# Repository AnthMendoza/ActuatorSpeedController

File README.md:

# FOC BLDC Servo Motor Controller

This board is a three phase field oriented control (FOC) motor controller for a brushless DC (BLDC) servo motor with an encoder. It combines a 32 bit microcontroller, a three-phase gate driver, six external power MOSFETs, phase current sensing, bus voltage sensing, motor temperature sensing, and encoder feedback.

## Functional overview

| Function | Main parts / nets | Purpose |
|---|---|---|
| MCU and control | STM32F405RGTx (U2) | Runs FOC, PWM generation, feedback processing, communications, and protection logic |
| Three-phase gate drive | DRV8323RSRGZT (U1) | Converts MCU PWM commands into high- and low-side MOSFET gate drive |
| Power stage | Q1-Q6, IQE022N06LM5CG | Six-switch inverter producing phase_A, phase_B, and phase_C |
| Current measurement | R8-R10, 1 mOhm | Low-side shunt current sensing for phases A, B, and C |
| Rotor position | AS5147U (shown on the drive sheet) | Magnetic encoder read over SPI; provides rotor angle feedback |
| DC-bus measurement | R11/R12, R14/R18, R16/R17 | Scales phase/bus-related sense nodes into MCU ADC inputs |
| Temperature measurement | R3 NTC 10k, R2 10k, C33 | Motor/board temperature input on `TEMP_MOTOR` / `ADC_TEMP` |
| Logic power | TPS62162DSG (U3) | Converts `+5V` to regulated `+3.3V` |
| CAN | TJA1051TK-3 (U4) | 3.3 V MCU CAN interface to `CANH` and `CANL` |
| USB | J4 USB-C | USB 2.0 device connection to the MCU; CC pull-downs are fitted |

## External connections

### DC bus:

| P1 pin | Schematic net | Description |
|---:|---|---|
| 1 | `GND` / `-Bat` | DC-bus negative |
| 2 | `+BATT` / `+Bat` | DC-bus positive |

`+BATT` feeds the DRV8323 power stage and the high-side MOSFET drains. `GND` is the power-stage return. Confirm the current board's polarity and connector orientation before connection.

### Encoder: AS5147U

| Encoder signal | Schematic net |
|---|---|
| VDD / VDD3V3 | `+3.3V` |
| Ground | `GND` |
| MOSI | `SPI3_MOSI` / `MOSI` |
| MISO | `SPI3_MISO` / `MISO` |
| CLK | `SPI3_SCK` / `CLK` |
| CSn | `SPI3_CS` / `CSn` |

## Control, debug, and communications

### SWD / service header

| Signal | Schematic label |
|---|---|
| CAN bus | `CAN_L`, `CAN_H` |
| Logic supply | `+3.3V` |
| Debug reset | `NRST` |
| Debug clock | `SWCLK` |
| Debug data | `SWDIO` |
| Return | `GND` |

### USB-C: J4

J4 is a USB 2.0 USB-C receptacle. The schematic connects:

- `D+` to MCU `USB_DP` through R4, 22 ohm.
- `D-` to MCU `USB_DM` through R21, 22 ohm.
- `CC1` and `CC2` to ground through R19 and R20, 5.1 kOhm.
- VBUS to `+5V`.
- Shield and USB ground to `GND` as shown.

USB is intended for MCU communication, programming, or diagnostics. It is not the motor-power input.

### CAN

U4, the TJA1051TK-3, translates MCU CAN signals to the differential bus:

- MCU `CAN_TX` -> U4 TXD
- MCU `CAN_RX` -> U4 RXD
- U4 `CANH` -> external `CANH`
- U4 `CANL` -> external `CANL`
- U4 VCC -> `+5V`
- U4 VIO -> `+3.3V`

## Internal signal map

| MCU function | Net(s) |
|---|---|
| Phase PWM control | `HA`, `HB`, `HC`, `LA`, `LB`, `LC` |
| Gate-driver enable | `EN_GATE` |
| Gate-driver fault | `FAULT` |
| Phase current ADCs | `CURRENT_A`, `CURRENT_B`, `CURRENT_C` |
| Temperature ADC | `TEMP_MOTOR` / `ADC_TEMP` |
| Phase/bus voltage ADCs | `VOLTAGE_A`, `VOLTAGE_B`, `VOLTAGE_C` |
| Encoder SPI | `SPI3_CS`, `SPI3_SCK`, `SPI3_MISO`, `SPI3_MOSI` |
| CAN | `CAN_TX`, `CAN_RX` |
| Servo input | `SERVO` |

## Power tree

```text
USB VBUS (+5V) -> TPS62162DSG -> +3.3V logic rail
DC bus (+BATT) -> DRV8323 VM and MOSFET bridge
DC bus return   -> GND / power-stage return
```

The logic rail has local decoupling at the MCU, encoder, gate driver, and regulator.

## Current and voltage sensing

- R8, R9, and R10 are shown as 1 mOhm low-side shunts for phases A, B, and C.
- The DRV8323 sense inputs are labelled `SOA`, `SOB`, and `SOC`.
- The MCU receives `CURRENT_A`, `CURRENT_B`, and `CURRENT_C`.
- Phase-voltage divider channels use 39 kOhm high-side resistors and 2.2 kOhm low-side resistors, with 1 uF filtering capacitors on the sense nodes.

## Configuration
```cpp
//Vesc pin definition for SPI control over DRV8323
#define DRV8323S_MOSI_GPIO      GPIOC
#define DRV8323S_MOSI_PIN       53      //PC12
#define DRV8323S_MISO_GPIO      GPIOC
#define DRV8323S_MISO_PIN       52      //PC11
#define DRV8323S_SCK_GPIO       GPIOC
#define DRV8323S_SCK_PIN        51      //PC10
#define DRV8323S_CS_GPIO        GPIOC
#define DRV8323S_CS_PIN         50      //PA15
```

```cpp
//Encoder definition for AS5x47u over SPI
#define HW_SPI_DEV              SPID1
#define HW_SPI_GPIO_AF          GPIO_AF_SPI1

#define HW_SPI_PORT_NSS         GPIOA   // AS5x47U CS
#define HW_SPI_PIN_NSS          4       // PA4

#define HW_SPI_PORT_SCK         GPIOA   // SCLK
#define HW_SPI_PIN_SCK          5       // PA5

#define HW_SPI_PORT_MOSI        GPIOA   // MOSI / SDI
#define HW_SPI_PIN_MOSI         7       // PA7

#define HW_SPI_PORT_MISO        GPIOA   // MISO / SDO
#define HW_SPI_PIN_MISO         6    

AS5x47U_config_t encoder_cfg_as5x47u = {
#ifdef HW_SPI_DEV
        &HW_SPI_DEV,

        {
                enc_as5x47u_spi_callback,
                HW_SPI_PORT_NSS,
                HW_SPI_PIN_NSS,
                SPI_BaudRatePrescaler_8 |
                SPI_CR1_CPHA |
                SPI_DATASIZE_8BIT
        },

        HW_SPI_GPIO_AF,
        HW_SPI_PORT_NSS,  HW_SPI_PIN_NSS,
        HW_SPI_PORT_SCK,  HW_SPI_PIN_SCK,
        HW_SPI_PORT_MOSI, HW_SPI_PIN_MOSI,
        HW_SPI_PORT_MISO, HW_SPI_PIN_MISO,
#endif
};
```

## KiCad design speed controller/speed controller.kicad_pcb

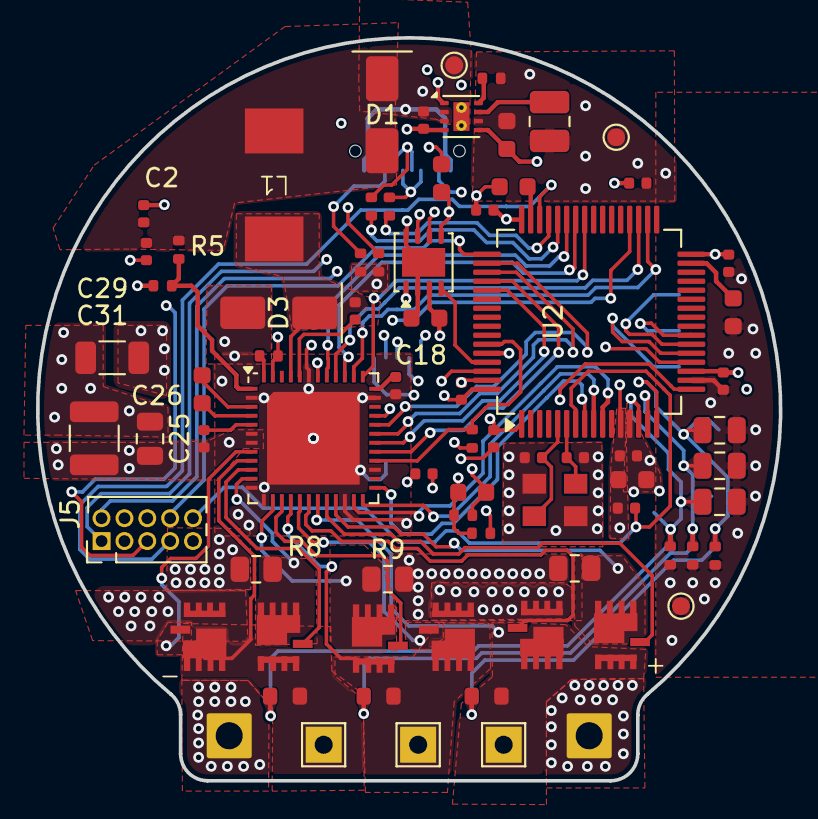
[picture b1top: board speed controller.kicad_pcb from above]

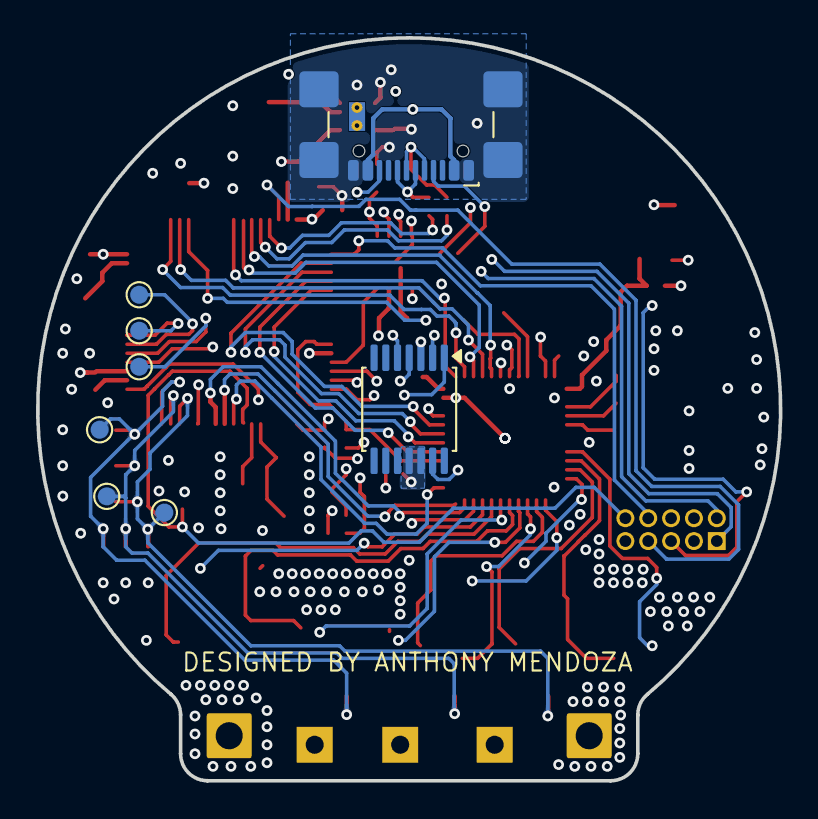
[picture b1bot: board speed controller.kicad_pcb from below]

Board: 4 copper layers, 41.3 x 41.3 mm, 82 parts (8 on the bottom side), 66 nets.

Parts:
C1, C5, C6: 1u; C_0805_2012Metric
C2, C4, C29: 10u; C_0402_1005Metric
C3: 22u; C_0603_1608Metric
C15, C16, C18, C32, C33: 2.2u; C_0603_1608Metric
C17, C19, C20, C21, C22, C30, C35, C37, C38: 100n; C_0402_1005Metric
C23: 1u; C_0603_1608Metric
C24: 4.7u; C_0402_1005Metric
C25, C39: 1u; C_0402_1005Metric
C26: 0.1u; C_0805_2012Metric
C27: 10u; C_1210_3225Metric
C28: 47n; C_0603_1608Metric
C31: 2.2u; C_1206_3216Metric
C34, C36: 10p; C_0402_1005Metric
D1: SS24; D_SMA
D3: SS110; D_SMA
J1, J2, J3: TestPoint_THTPad_2.0x2.0mm_Drill1.0mm
J4: USB_C_Receptacle_USB2.0_16P; USB_C_Receptacle_GCT_USB4110
J5: Conn_02x05_Counter_Clockwise; PinHeader_2x05_P1.27mm_Vertical
L1: 22u; DR74
L2: 2.2u; L_1008_2520Metric
P1: Power Pads
Q1, Q2, Q3, Q4, Q5, Q6: IQE022N06LM5CG; PG-TTFN-9-3
R2, R13, R15: 10k; R_0402_1005Metric
R3: NTC 10k; R_0402_1005Metric
R4, R21: 22; R_0402_1005Metric
R5: 54.9k; R_0402_1005Metric
R6, R7: 100k; R_0402_1005Metric
R8, R9, R10: 1m; R_0805_2012Metric
R11, R14, R16: 39k; R_0603_1608Metric
R12, R17, R18: 2.2k; R_0402_1005Metric
R19, R20: 5.1k; R_0402_1005Metric
TP1, TP2, TP3, TP4, TP5, TP6, TP7, TP8, TP9: TestPoint_Probe; TestPoint_Pad_D1.0mm
U1: DRV8323RSRGZT; Infineon_MLPQ-48-1EP_7x7mm_P0.5mm_EP5.15x5.15mm
U2: STM32F405RGTx; LQFP-64_10x10mm_P0.5mm
U3: TPS62162DSG; WSON-8-1EP_2x2mm_P0.5mm_EP0.9x1.6mm_ThermalVias
U4: TJA1051TK-3; HVSON-8-1EP_3x3mm_P0.65mm_EP1.6x2.4mm
Y1: ECS-80-8-33-JGN-TR3
h1: TSSOP-14_4.4x5mm_P0.65mm

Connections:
+3.3V: C3.1, C17.1, C19.1, C20.1, C21.1, C22.2, C23.2, C24.1, C32.1, C37.1, C38.1, J5.5, L2.2, R3.1, R7.2, R13.1, TP1.1 (1_1), U2.1 (VBAT), U2.13 (VDDA), U2.19 (VDD), U2.32 (VDD), U2.48 (VDD), U2.64 (VDD), U3.6 (VOS), U4.5 (VIO), h1.11 (VDD), h1.12 (VDD3V3)
+5V: C4.1, C18.1, D1.1 (K), J4.A4 (VBUS), J4.A9 (VBUS), J4.B4 (VBUS), J4.B9 (VBUS), TP3.1 (1_1), U3.2 (VIN), U3.3 (EN), U4.3 (VCC)
+BATT: C25.1, C26.1, C27.1, C31.1, P1.2 (+Bat), Q1.2 (D), Q3.2 (D), Q5.2 (D), R6.1, U1.6 (VM), U1.7 (VDRAIN), U1.47 (VIN)
/CAN_H: J5.2, U4.7 (CANH)
/CAN_L: J5.1, U4.6 (CANL)
/CAN_Transceiver/CAN_RX: U2.61 (PB8), U4.4 (RXD)
/CAN_Transceiver/CAN_TX: U2.62 (PB9), U4.1 (TXD)
/DRV8323RSRGZT/Fault: R13.2, U1.28 (FAULT_N), U2.59 (PB7)
/DRV8323RSRGZT/GHA: Q1.1 (G), U1.8 (GHA)
/DRV8323RSRGZT/GHB: Q3.1 (G), U1.17 (GHB)
/DRV8323RSRGZT/GHC: Q5.1 (G), U1.18 (GHC)
/DRV8323RSRGZT/GLA: Q2.1 (G), U1.10 (GLA)
/DRV8323RSRGZT/GLB: Q4.1 (G), U1.15 (GLB)
/DRV8323RSRGZT/GLC: Q6.1 (G), U1.20 (GLC)
/DRV8323RSRGZT/INHA: U1.37 (INHA), U2.41 (PA8)
/DRV8323RSRGZT/INHB: U1.39 (INHB), U2.42 (PA9)
/DRV8323RSRGZT/INHC: U1.41 (INHC), U2.43 (PA10)
/DRV8323RSRGZT/INLA: U1.38 (INLA), U2.34 (PB13)
/DRV8323RSRGZT/INLB: U1.40 (INLB), U2.35 (PB14)
/DRV8323RSRGZT/INLC: U1.42 (INLC), U2.36 (PB15)
/DRV8323RSRGZT/SCLK: U1.31 (SCLK), U2.51 (PC10)
/DRV8323RSRGZT/SCS_N: U1.32 (SCS_N), U2.50 (PA15)
/DRV8323RSRGZT/SDI: U1.30 (SDI), U2.53 (PC12)
/DRV8323RSRGZT/SDO: U1.29 (SDO), U2.52 (PC11)
/DRV8323RSRGZT/SHDN: R6.2, U1.48 (SHDN_N)
/DRV8323RSRGZT/SOA: U1.25 (SOA), U2.8 (PC0)
/DRV8323RSRGZT/SOB: U1.24 (SOB), U2.9 (PC1)
/DRV8323RSRGZT/SOC: U1.23 (SOC), U2.10 (PC2)
/DRV8323RSRGZT/SPA: Q2.3 (S), R8.1, U1.11 (SPA)
/DRV8323RSRGZT/SPB: Q4.3 (S), R9.1, U1.14 (SPB)
/DRV8323RSRGZT/SPC: Q6.3 (S), R10.1, U1.21 (SPC)
/STM32F405RGTx/ADC_TEMP: C33.1, R2.1, R3.2, U2.17 (PA3)
/STM32F405RGTx/NRST: C35.1, J5.10, U2.7 (NRST)
/STM32F405RGTx/PG: R7.1, U3.8 (PG)
/STM32F405RGTx/PH0_OSC_IN: C34.1, U2.5 (PH0), Y1.1 (IN/OUT)
/STM32F405RGTx/PH1_OSC_OUT: C36.1, U2.6 (PH1), Y1.3 (OUT/IN)
/STM32F405RGTx/SPI_1_MISO: TP5.1 (1_1), U2.22 (PA6), h1.3 (MISO)
/STM32F405RGTx/SPI_1_MOSI: TP4.1 (1_1), U2.23 (PA7), h1.4 (MOSI)
/STM32F405RGTx/SPI_1_NSS: U2.20 (PA4), h1.1 (CSn)
/STM32F405RGTx/SPI_1_SCK: TP6.1 (1_1), U2.21 (PA5), h1.2 (CLK)
/STM32F405RGTx/SWCLK: J5.8, U2.49 (PA14)
/STM32F405RGTx/SWDIO: J5.7, U2.46 (PA13)
/STM32F405RGTx/USB_DM: R21.2, U2.44 (PA11)
/STM32F405RGTx/USB_DP: R4.2, U2.45 (PA12)
/STM32F405RGTx/VOLTAGE_A: C1.1, R11.2, R12.1, TP7.1 (1_1), U2.14 (PA0)
/STM32F405RGTx/VOLTAGE_B: C5.1, R14.2, R18.1, TP8.1 (1_1), U2.15 (PA1)
/STM32F405RGTx/VOLTAGE_C: C6.1, R16.2, R17.1, TP9.1 (1_1), U2.16 (PA2)
/drive/phase_A: J1.1 (phase_1), Q1.3 (S), Q2.2 (D), R11.1, U1.9 (SHA)
/drive/phase_B: J2.1 (phase_1), Q3.3 (S), Q4.2 (D), R14.1, U1.16 (SHB)
/drive/phase_C: J3.1 (phase_1), Q5.3 (S), Q6.2 (D), R16.1, U1.19 (SHC)
GND: C1.2, C2.2, C3.2, C4.2, C5.2, C6.2, C15.2, C16.2, C17.2, C18.2, C19.2, C20.2, C21.2, C22.1, C23.1, C24.2, C26.2, C27.2, C29.2, C31.2, C32.2, C33.2, C34.2, C35.2, C36.2, C37.2, C38.2, C39.2, D3.2 (A), J4.A1 (GND), J4.A12 (GND), J4.B1 (GND), J4.B12 (GND), J4.SH (SHIELD), J5.6, P1.1 (-Bat), R2.2, R8.2, R9.2, R10.2, R12.2, R15.2, R17.2, R18.2, R19.2, R20.2, TP2.1 (1_1), U1.2 (PGND), U1.12 (SNA), U1.13 (SNB), U1.22 (SNC), U1.27 (DGND), U1.35 (AGND), U1.43 (BGND), U1.49 (EP), U2.12 (VSSA), U2.18 (VSS), U2.60 (BOOT0), U2.63 (VSS), U3.1 (PGND), U3.4 (AGND), U3.5 (FB), U4.2 (GND), U4.8 (S), U4.9 (GND), Y1.2 (GND_1), Y1.4 (GND_2), h1.5 (TEST), h1.13 (GND)
unnamed: C2.1, C29.1, D1.2 (A), L1.2, R5.1
unnamed: C30.2, D3.1 (K), L1.1, U1.45 (SW)
unnamed: J4.A5 (CC1), R19.1
unnamed: J4.B5 (CC2), R20.1
unnamed: J4.A6 (D+), J4.B6 (D+), R4.1
unnamed: J4.A7 (D-), J4.B7 (D-), R21.1
unnamed: C30.1, U1.44 (CB)
unnamed: C28.1, U1.4 (CPH)
unnamed: C28.2, U1.3 (CPL)
unnamed: C39.1, U1.36 (DVDD)
unnamed: R5.2, R15.1, U1.1 (FB)
unnamed: C25.2, U1.5 (VCP)
unnamed: C16.1, U2.31 (VCAP_1)
unnamed: C15.1, U2.47 (VCAP_2)
unnamed: L2.1, U3.7 (SW)
